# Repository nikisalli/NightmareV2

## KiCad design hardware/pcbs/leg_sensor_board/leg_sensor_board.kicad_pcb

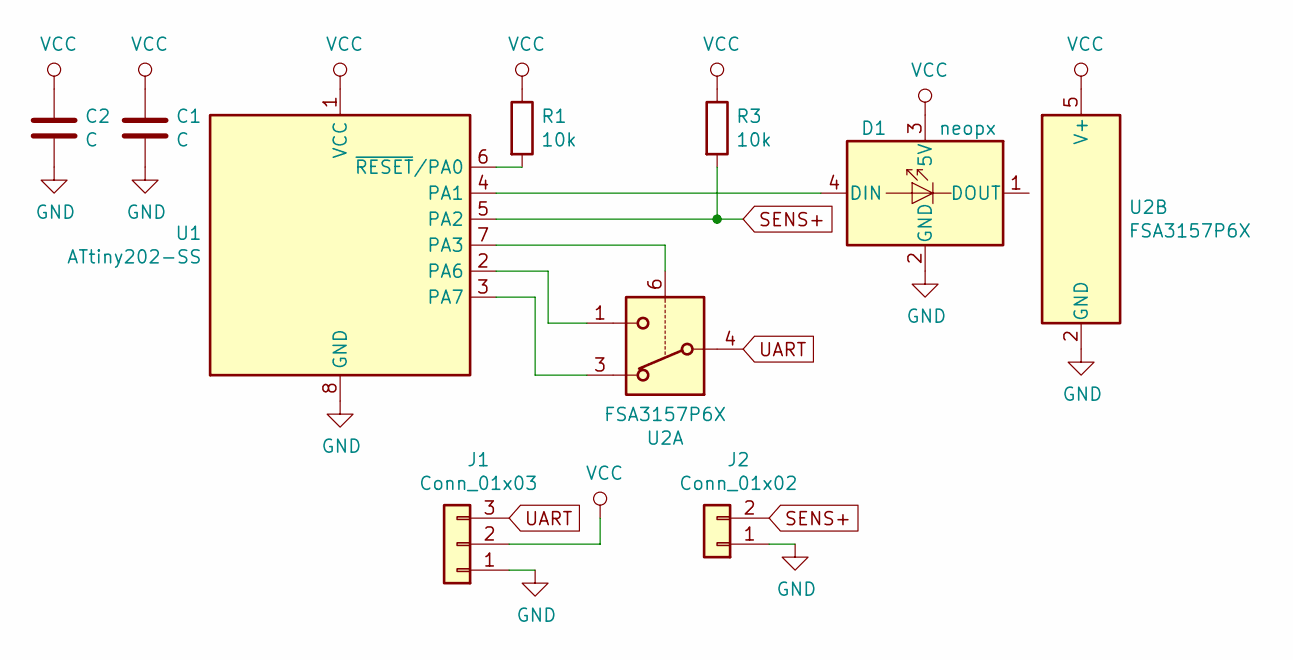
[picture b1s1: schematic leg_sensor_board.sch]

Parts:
C1, C2: C; C_0603_1608Metric
D1: neopx; LED_WS2812B_PLCC4_5.0x5.0mm_P3.2mm
J1: Conn_01x03; PinHeader_1x03_P2.54mm_Vertical
J2: Conn_01x02; PinHeader_1x02_P2.54mm_Vertical
R1, R3: 10k; R_0603_1608Metric
U1: ATtiny202-SS; SOIC-8_3.9x4.9mm_P1.27mm
U2: FSA3157P6X; SOT-363_SC-70-6

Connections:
GND: C1.2, C2.2, D1.2 (GND), J1.1, J2.1, U1.8 (GND), U2.2 (GND)
unnamed: D1.4 (DIN), U1.4 (PA1)
unnamed: R1.2, U1.6 (~RESET~/PA0)
unnamed: U1.2 (PA6), U2.1
unnamed: U1.3 (PA7), U2.3
unnamed: U1.7 (PA3), U2.6
SENS+: J2.2, R3.2, U1.5 (PA2)
UART: J1.3, U2.4
VCC: C1.1, C2.1, D1.3 (5V), J1.2, R1.1, R3.1, U1.1 (VCC), U2.5 (V+)

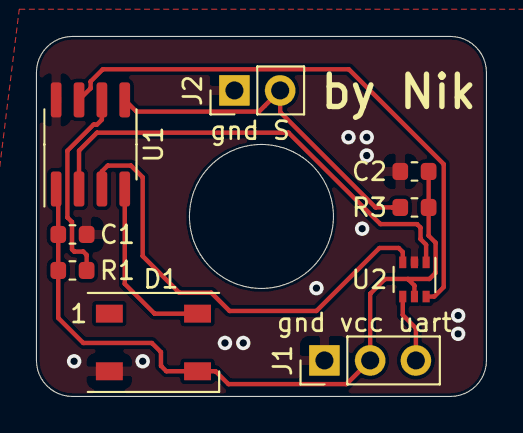
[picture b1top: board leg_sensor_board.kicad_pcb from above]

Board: 2 copper layers, 25.0 x 20.0 mm, 9 parts (0 on the bottom side), 9 nets.

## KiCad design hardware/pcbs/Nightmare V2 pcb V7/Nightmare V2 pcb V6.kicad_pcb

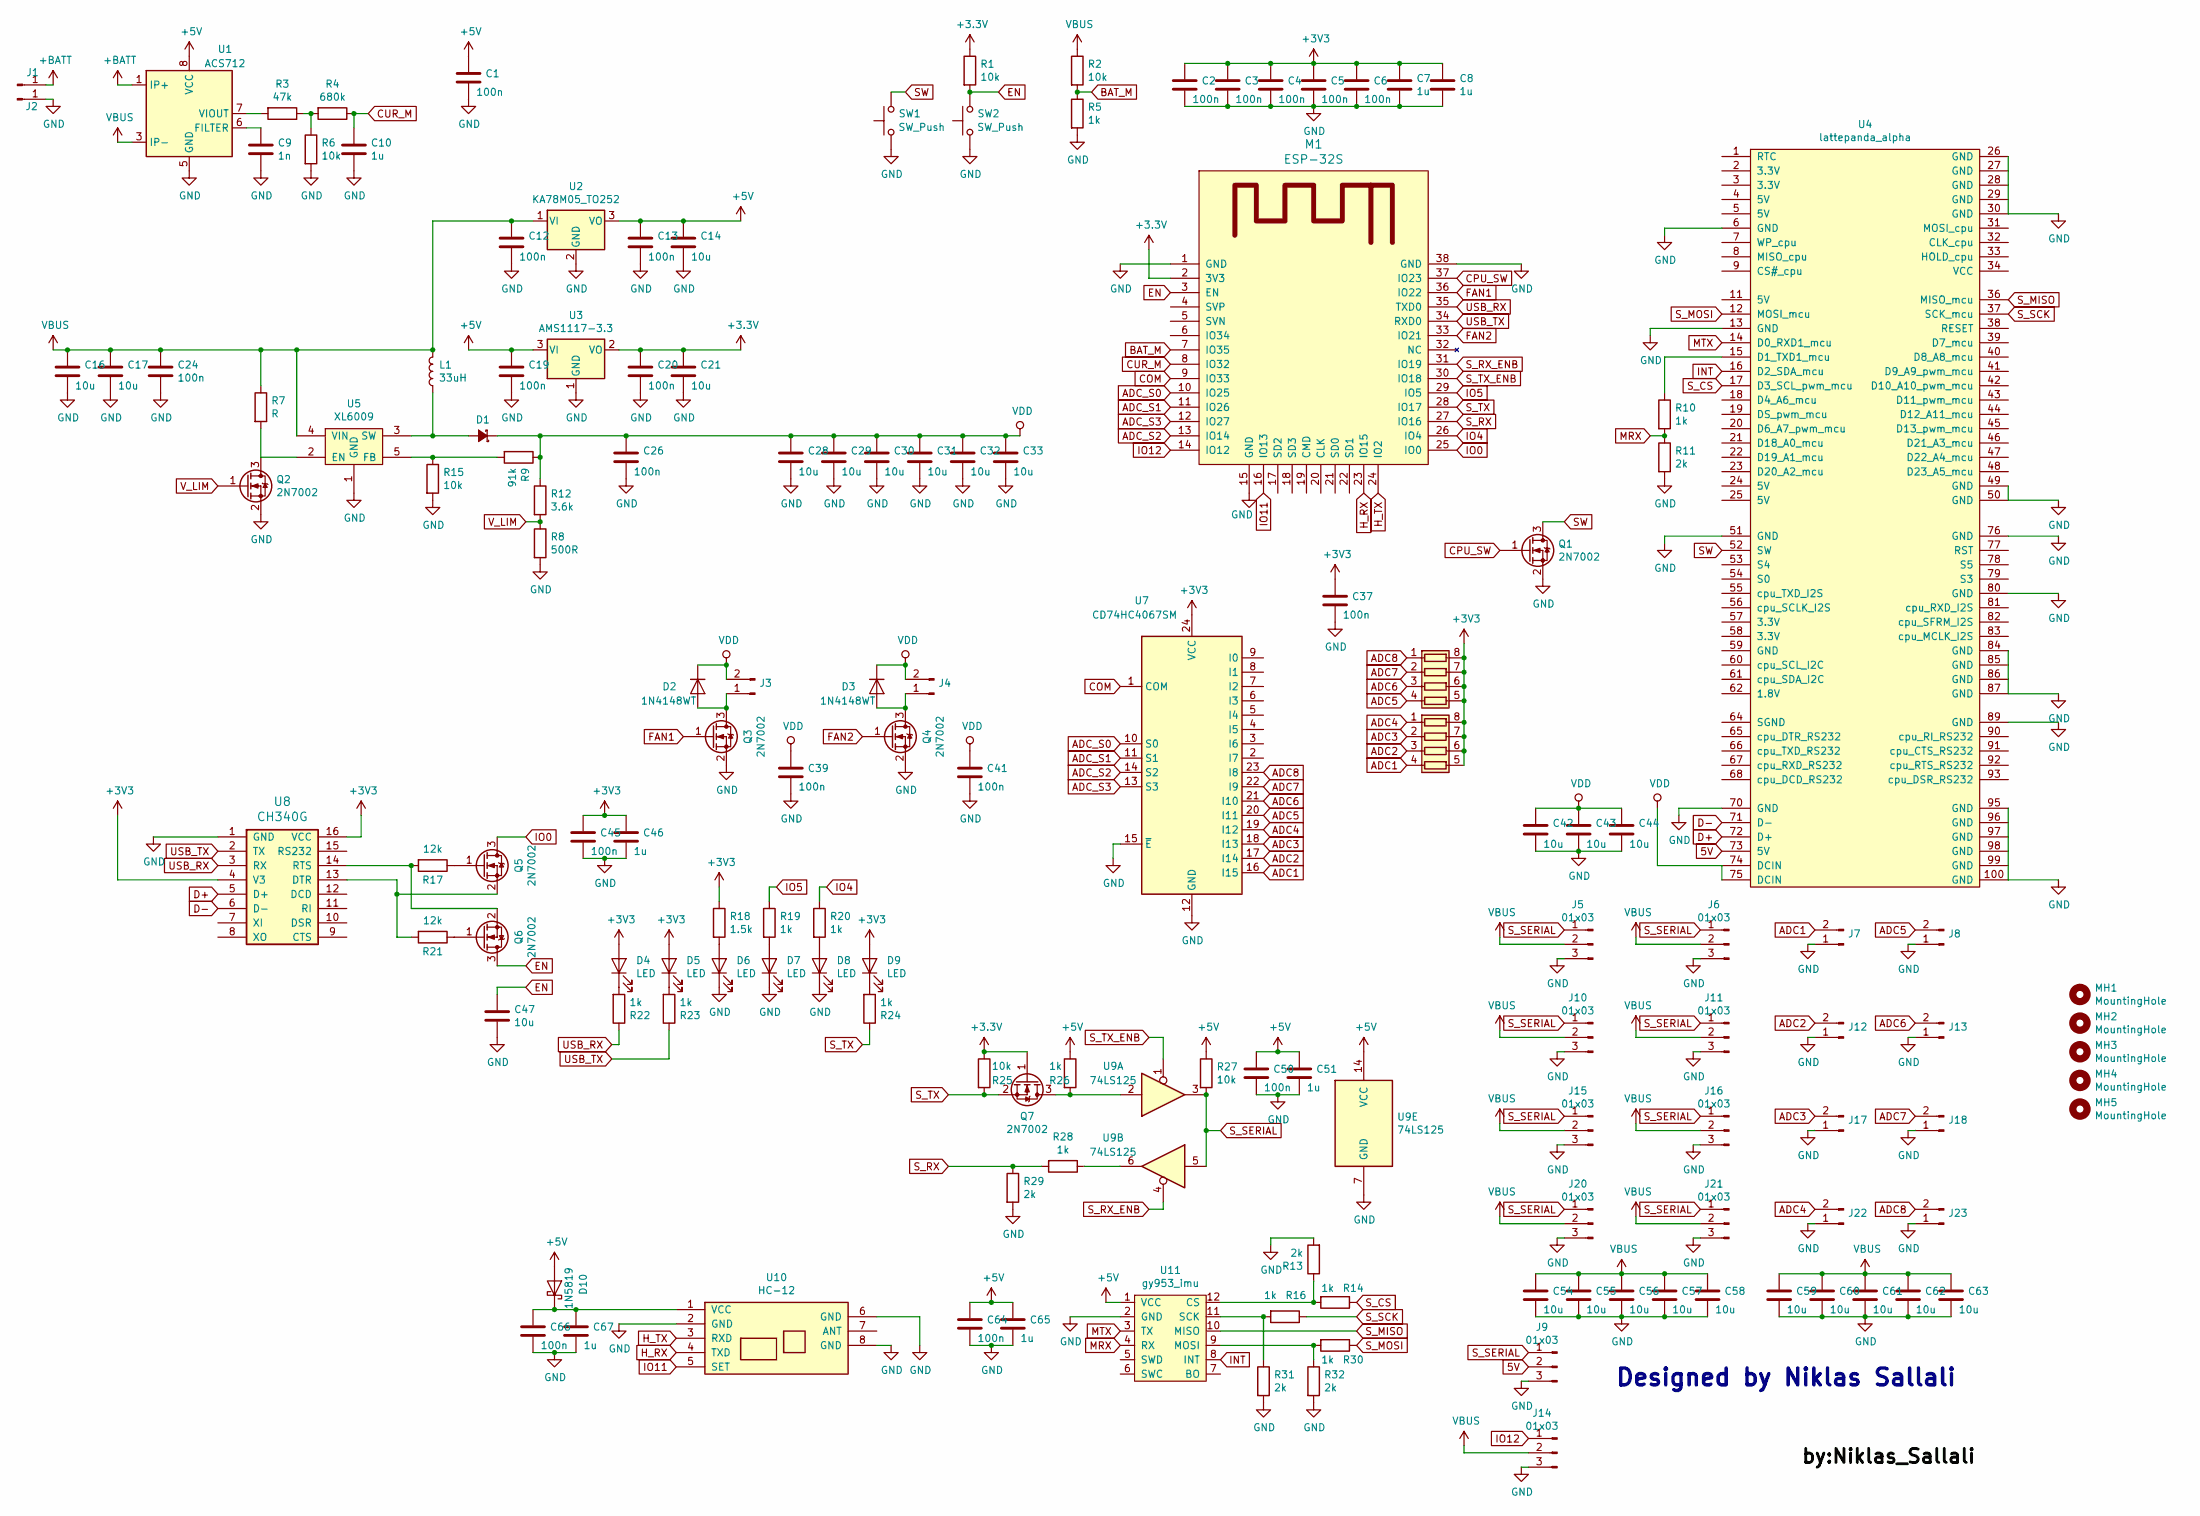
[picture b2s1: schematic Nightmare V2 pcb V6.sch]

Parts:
C1, C2, C3, C4, C5, C6, C12, C13, C19, C20, C24, C26, C37, C39, C41, C45, C50, C64, C66: 100n; C_0603_1608Metric
C7, C8, C10, C46, C51, C65, C67: 1u; C_0603_1608Metric
C9: 1n; C_0603_1608Metric
C14, C16, C17, C21, C28, C29, C30, C31, C32, C33, C42, C43, C44, C47, C54, C55, C56, C57, C58, C59, C60, C61, C62, C63: 10u; C_1206_3216Metric
D1: SS510; D_SMC; PartNumber LSM115JE3/TR13CT-ND
D2, D3: 1N4148WT; D_SOD-523
D4, D5, D6, D7, D8, D9: LED; LED_0603_1608Metric_Pad1.05x0.95mm_HandSolder
D10: 1N5819; D_SMA
J1, J2: Conn_01x01_Male; TestPoint_THTPad_4.0x4.0mm_Drill2.0mm
J3, J4: Conn_01x02_Male; JST_XH_B02B-XH-A_1x02_P2.50mm_Vertical
J5, J6, J9, J10, J11, J14, J15, J16, J20, J21: 01x03; JST_XH_B03B-XH-A_1x03_P2.50mm_Vertical
J7, J8, J12, J13, J17, J18, J22, J23: Conn_01x02_Male; JST_SH_BM02B-SRSS-TB_1x02-1MP_P1.00mm_Vertical
L1: 33uH; L_12x12mm_H6mm
M1: ESP-32S
MH1, MH2, MH3, MH4: MountingHole; MountingHole_3.2mm_M3_DIN965_Pad
MH5: MountingHole; nik_logo_15x13
Q1, Q2, Q3, Q4, Q5, Q6, Q7: 2N7002; SOT-23
R1, R2, R6, R15, R25, R27: 10k; R_0603_1608Metric
R3: 47k; R_0603_1608Metric
R4: 680k; R_0603_1608Metric
R5, R10, R14, R16, R19, R20, R22, R23, R24, R26, R28, R30: 1k; R_0603_1608Metric
R7: R; R_0603_1608Metric
R8: 500R; R_0603_1608Metric
R9: 91k; R_0603_1608Metric
R11, R13, R29, R31, R32: 2k; R_0603_1608Metric
R12: 3.6k; R_0603_1608Metric
R17, R21: 12k; R_0603_1608Metric
R18: 1.5k; R_0603_1608Metric
RN2, RN3: R_Pack04; R_Array_Convex_4x0603
SW1, SW2: SW_Push; SW_SPST_SKQG_WithoutStem
U1: ACS712; SOIC-8_3.9x4.9mm_P1.27mm
U2: KA78M05_TO252; TO-252-2
U3: AMS1117-3.3; SOT-223-3_TabPin2
U4: lattepanda_alpha
U5: XL6009; TO-263-5_TabPin3
U7: CD74HC4067SM; SSOP-24_5.3x8.2mm_P0.65mm
U8: CH340G; SOIC-16_3.9x9.9mm_P1.27mm
U9: 74LS125; SOIC-14_3.9x8.7mm_P1.27mm
U10: HC-12
U11: gy953_imu; GY953_IMU

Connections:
5V: J9.2, U4.73 (5V)
+5V: C1.1, C13.1, C14.1, C19.1, C50.1, C51.1, C64.1, C65.1, D10.2 (A), R26.1, R27.1, U1.8 (VCC), U2.3 (VO), U3.3 (VI), U9.14 (VCC), U11.1 (VCC)
+BATT: J1.1, U1.1 (IP+), U1.2 (IP+)
ADC1: J7.2, RN3.4 (R4.1), U7.16 (I15)
ADC2: J12.2, RN3.3 (R3.1), U7.17 (I14)
ADC3: J17.2, RN3.2 (R2.1), U7.18 (I13)
ADC4: J22.2, RN3.1 (R1.1), U7.19 (I12)
ADC5: J8.2, RN2.4 (R4.1), U7.20 (I11)
ADC6: J13.2, RN2.3 (R3.1), U7.21 (I10)
ADC7: J18.2, RN2.2 (R2.1), U7.22 (I9)
ADC8: J23.2, RN2.1 (R1.1), U7.23 (I8)
ADC_S0: M1.10 (IO25), U7.10 (S0)
ADC_S1: M1.11 (IO26), U7.11 (S1)
ADC_S2: M1.13 (IO14), U7.14 (S2)
ADC_S3: M1.12 (IO27), U7.13 (S3)
BAT_M: M1.7 (IO35), R2.2, R5.1
COM: M1.9 (IO33), U7.1 (COM)
CPU_SW: M1.37 (IO23), Q1.1 (G)
CUR_M: C10.1, M1.8 (IO32), R4.1
D+: U4.72 (D+), U8.5 (D+)
D-: U4.71 (D-), U8.6 (D-)
EN: C47.1, M1.3 (EN), Q6.3 (D), R1.2, SW2.2
FAN1: M1.36 (IO22), Q3.1 (G)
FAN2: M1.33 (IO21), Q4.1 (G)
GND: C1.2, C2.2, C3.2, C4.2, C5.2, C6.2, C7.2, C8.2, C9.2, C10.2, C12.2, C13.2, C14.2, C16.2, C17.2, C19.2, C20.2, C21.2, C24.2, C26.2, C28.2, C29.2, C30.2, C31.2, C32.2, C33.2, C37.2, C39.2, C41.2, C42.2, C43.2, C44.2, C45.2, C46.2, C47.2, C50.2, C51.2, C54.2, C55.2, C56.2, C57.2, C58.2, C59.2, C60.2, C61.2, C62.2, C63.2, C64.2, C65.2, C66.2, C67.2, D6.1 (K), D7.1 (K), D8.1 (K), J2.1, J5.3, J6.3, J7.1, J8.1, J9.3, J10.3, J11.3, J12.1, J13.1, J14.3, J15.3, J16.3, J17.1, J18.1, J20.3, J21.3, J22.1, J23.1, M1.1 (GND), M1.15 (GND), M1.38 (GND), Q1.2 (S), Q2.2 (S), Q3.2 (S), Q4.2 (S), R5.2, R6.2, R8.2, R11.2, R13.2, R15.2, R29.2, R31.2, R32.2, SW1.1, SW2.1, U1.5 (GND), U2.2 (GND), U3.1 (GND), U4.6 (GND), U4.13 (GND), U4.26 (GND), U4.30 (GND), U4.49 (GND), U4.50 (GND), U4.51 (GND), U4.70 (GND), U4.76 (GND), U4.80 (GND), U4.84 (GND), U4.87 (GND), U4.89 (GND), U4.95 (GND), U4.100 (GND), U5.1 (GND), U7.12 (GND), U7.15 (~E), U8.1 (GND), U9.7 (GND), U10.2 (GND), U10.6 (GND), U10.8 (GND), U11.2 (GND)
H_RX: M1.23 (IO15), U10.4 (TXD)
H_TX: M1.24 (IO2), U10.3 (RXD)
INT: U4.16 (D2_SDA_mcu), U11.8 (INT)
IO0: M1.25 (IO0), Q5.3 (D)
IO4: M1.26 (IO4), R20.1
IO5: M1.29 (IO5), R19.1
IO11: M1.16 (IO13), U10.5 (SET)
IO12: J14.1, M1.14 (IO12)
MRX: R10.2, R11.1, U11.4 (RX)
MTX: U4.14 (D0_RXD1_mcu), U11.3 (TX)
unnamed: C9.1, U1.6 (FILTER)
unnamed: C66.1, C67.1, D10.1 (K), U10.1 (VCC)
unnamed: D1.2 (A), L1.1, U5.3 (SW)
unnamed: D2.2 (A), J3.1, Q3.3 (D)
unnamed: D3.2 (A), J4.1, Q4.3 (D)
unnamed: D4.1 (K), R22.2
unnamed: D5.1 (K), R23.2
unnamed: D6.2 (A), R18.2
unnamed: D7.2 (A), R19.2
unnamed: D8.2 (A), R20.2
unnamed: D9.1 (K), R24.2
unnamed: Q2.3 (D), R7.2, U5.2 (EN)
unnamed: Q5.1 (G), R17.1
unnamed: Q5.2 (S), R21.2, U8.13 (DTR)
unnamed: Q6.1 (G), R21.1
unnamed: Q6.2 (S), R17.2, U8.14 (RTS)
unnamed: Q7.3 (D), R26.2, U9.2
unnamed: R3.1, R4.2, R6.1
unnamed: R3.2, U1.7 (VIOUT)
unnamed: R10.1, U4.15 (D1_TXD1_mcu)
unnamed: R13.1, R14.2, U11.12 (CS)
unnamed: R9.2, R15.1, U5.5 (FB)
unnamed: R16.2, R31.1, U11.11 (SCK)
unnamed: R28.1, U9.6
unnamed: R30.2, R32.1, U11.9 (MOSI)
SW: Q1.3 (D), SW1.2, U4.52 (SW)
S_CS: R14.1, U4.17 (D3_SCL_pwm_mcu)
S_MISO: U4.36 (MISO_mcu), U11.10 (MISO)
S_MOSI: R30.1, U4.12 (MOSI_mcu)
S_RX: M1.27 (IO16), R28.2, R29.1
S_RX_ENB: M1.31 (IO19), U9.4
S_SCK: R16.1, U4.37 (SCK_mcu)
S_SERIAL: J5.1, J6.1, J9.1, J10.1, J11.1, J15.1, J16.1, J20.1, J21.1, R27.2, U9.3, U9.5
S_TX: M1.28 (IO17), Q7.2 (S), R24.1, R25.2
S_TX_ENB: M1.30 (IO18), U9.1
USB_RX: M1.35 (TXD0), R22.1, U8.3 (RX)
USB_TX: M1.34 (RXD0), R23.1, U8.2 (TX)
VBUS: C12.1, C16.1, C17.1, C24.1, C54.1, C55.1, C56.1, C57.1, C58.1, C59.1, C60.1, C61.1, C62.1, C63.1, J5.2, J6.2, J10.2, J11.2, J14.2, J15.2, J16.2, J20.2, J21.2, L1.2, R2.1, R7.1, U1.3 (IP-), U1.4 (IP-), U2.1 (VI), U5.4 (VIN)
VDD: C26.1, C28.1, C29.1, C30.1, C31.1, C32.1, C33.1, C39.1, C41.1, C42.1, C43.1, C44.1, D1.1 (K), D2.1 (K), D3.1 (K), J3.2, J4.2, R9.1, R12.1, U4.74 (DCIN), U4.75 (DCIN)
V_LIM: Q2.1 (G), R8.1, R12.2

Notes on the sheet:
Designed by Niklas Sallali

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
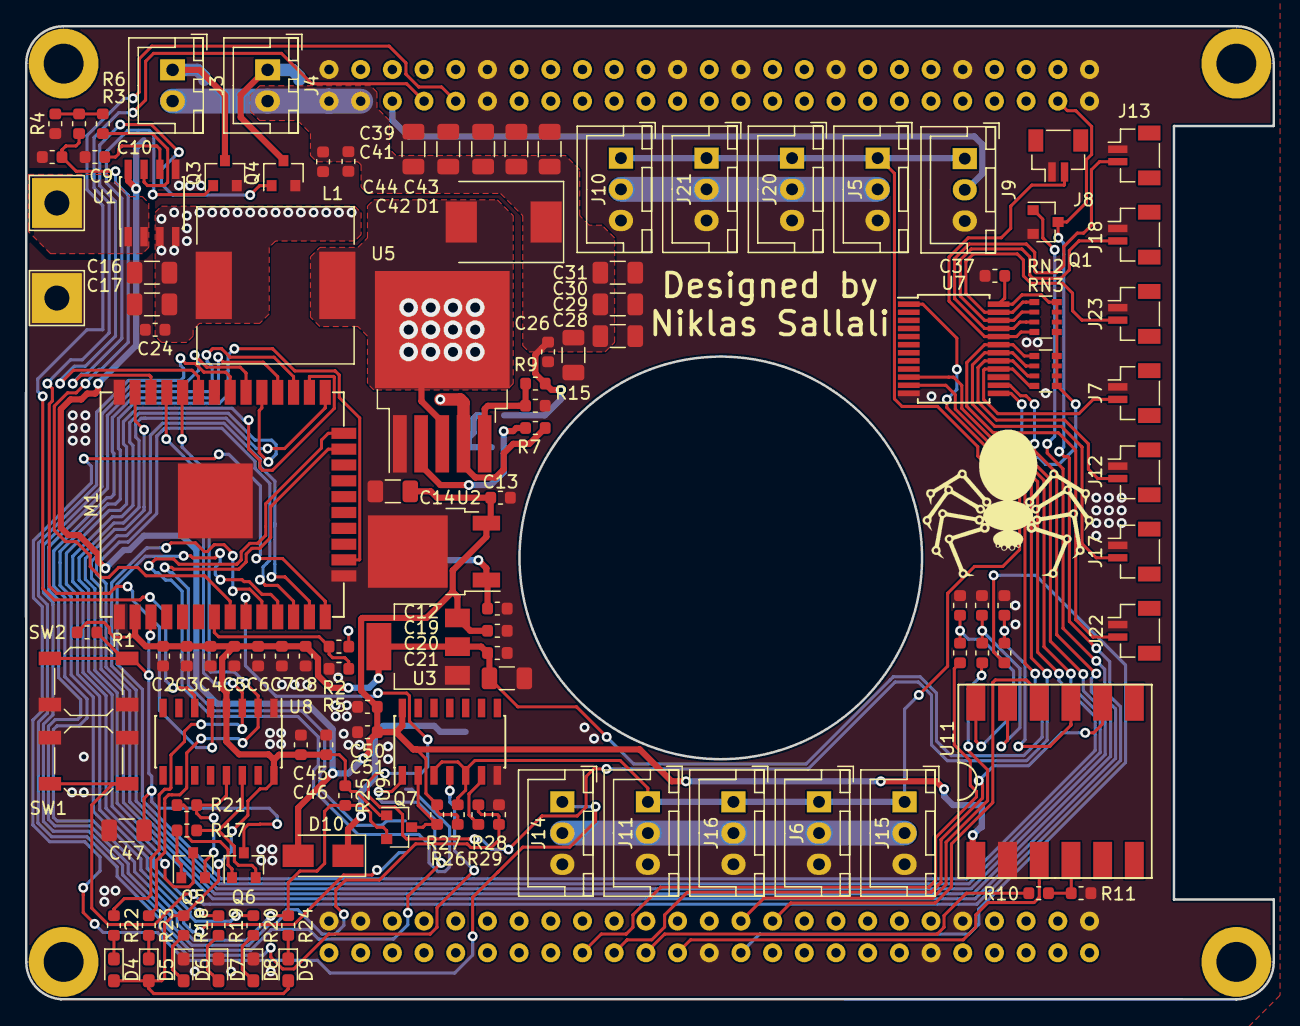
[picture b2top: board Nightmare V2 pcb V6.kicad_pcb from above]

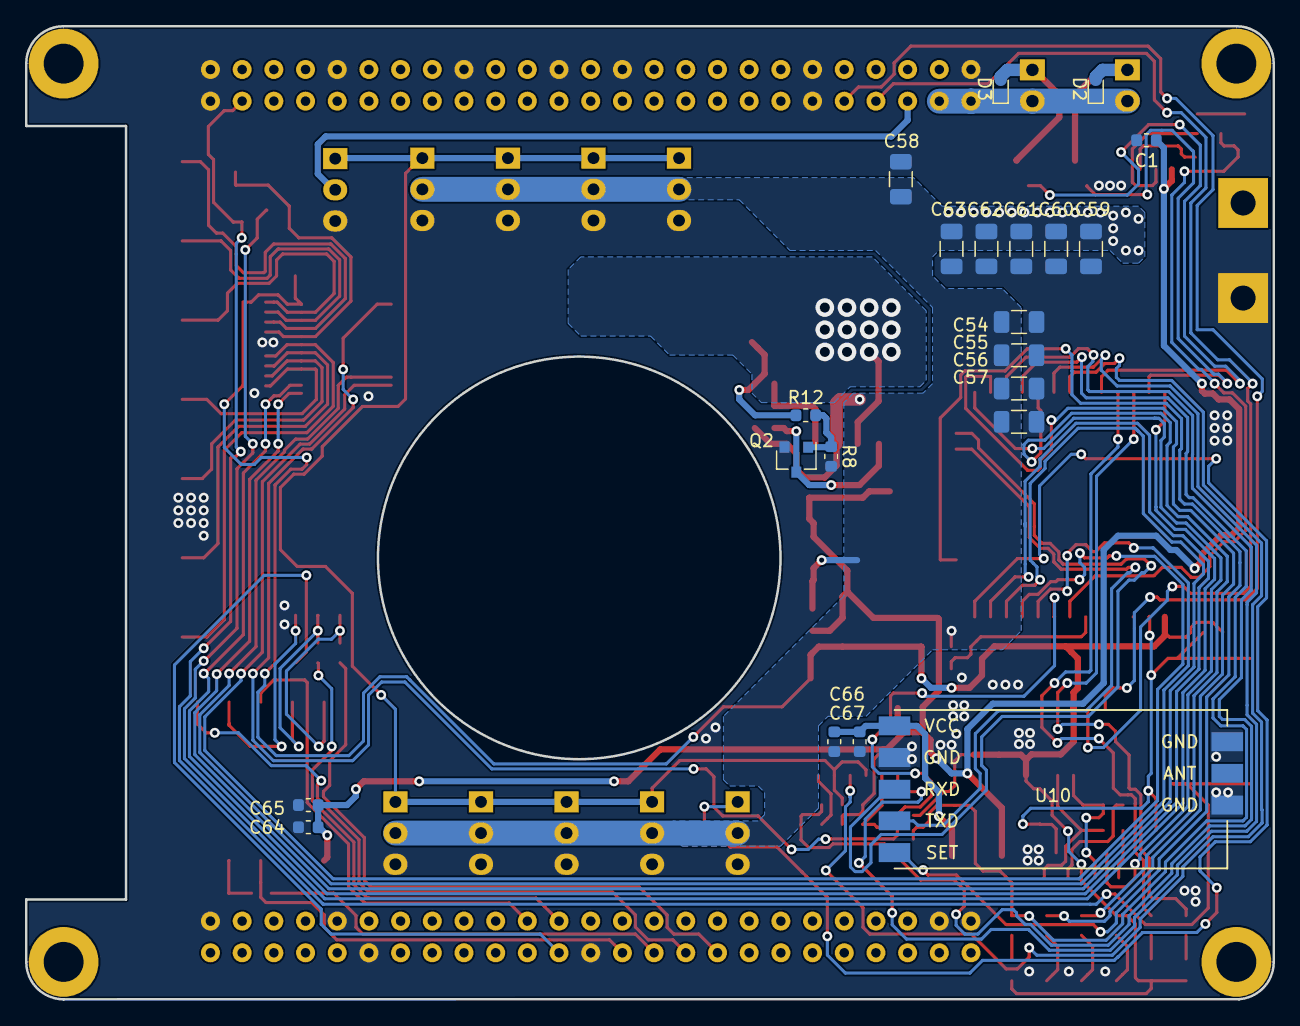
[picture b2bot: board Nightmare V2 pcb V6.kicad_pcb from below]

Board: 2 copper layers, 100.0 x 78.0 mm, 143 parts (21 on the bottom side), 76 nets.

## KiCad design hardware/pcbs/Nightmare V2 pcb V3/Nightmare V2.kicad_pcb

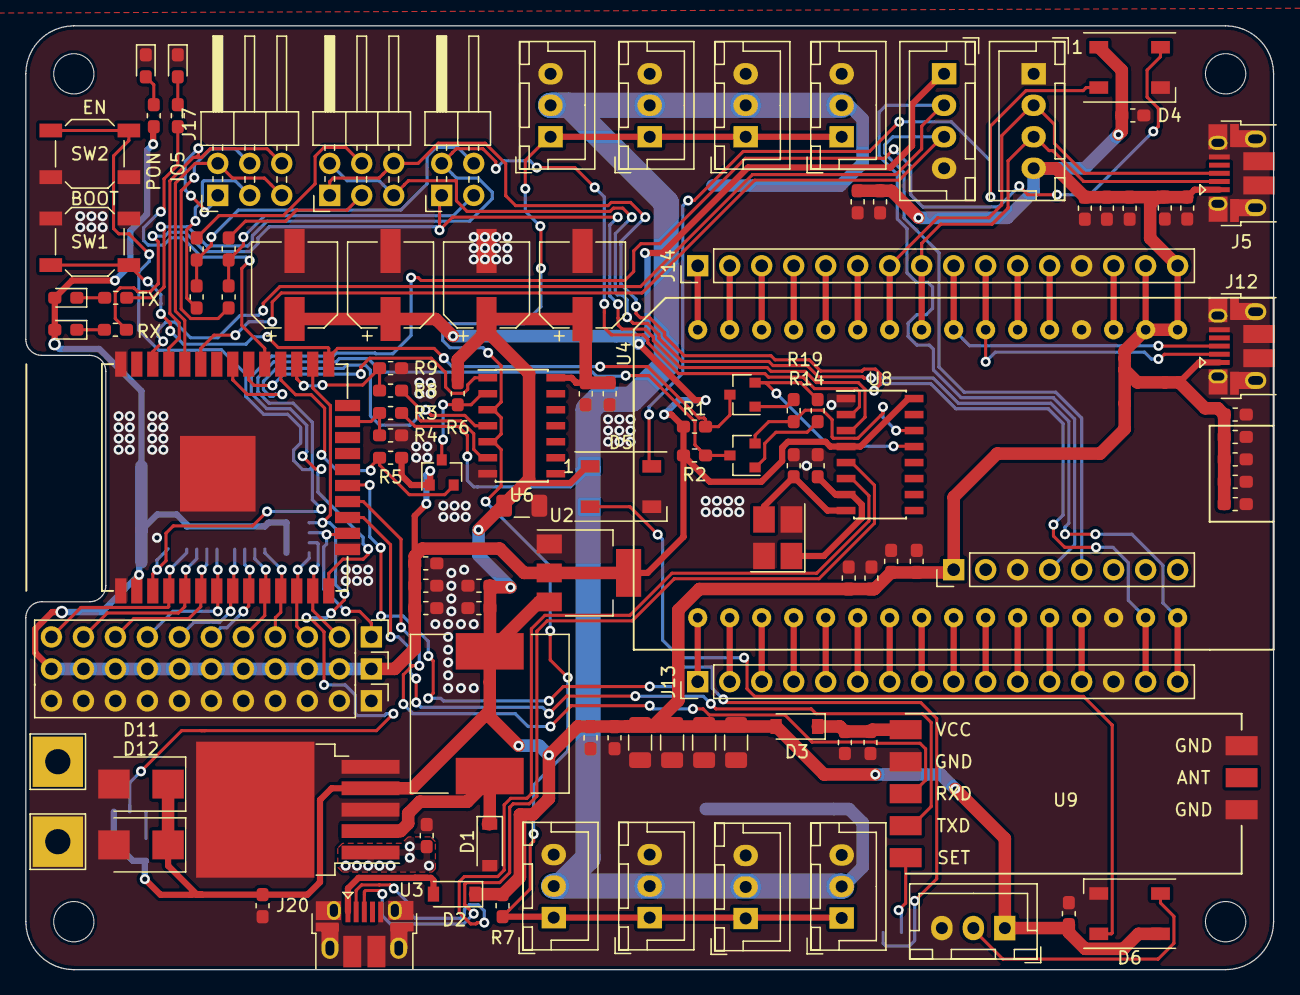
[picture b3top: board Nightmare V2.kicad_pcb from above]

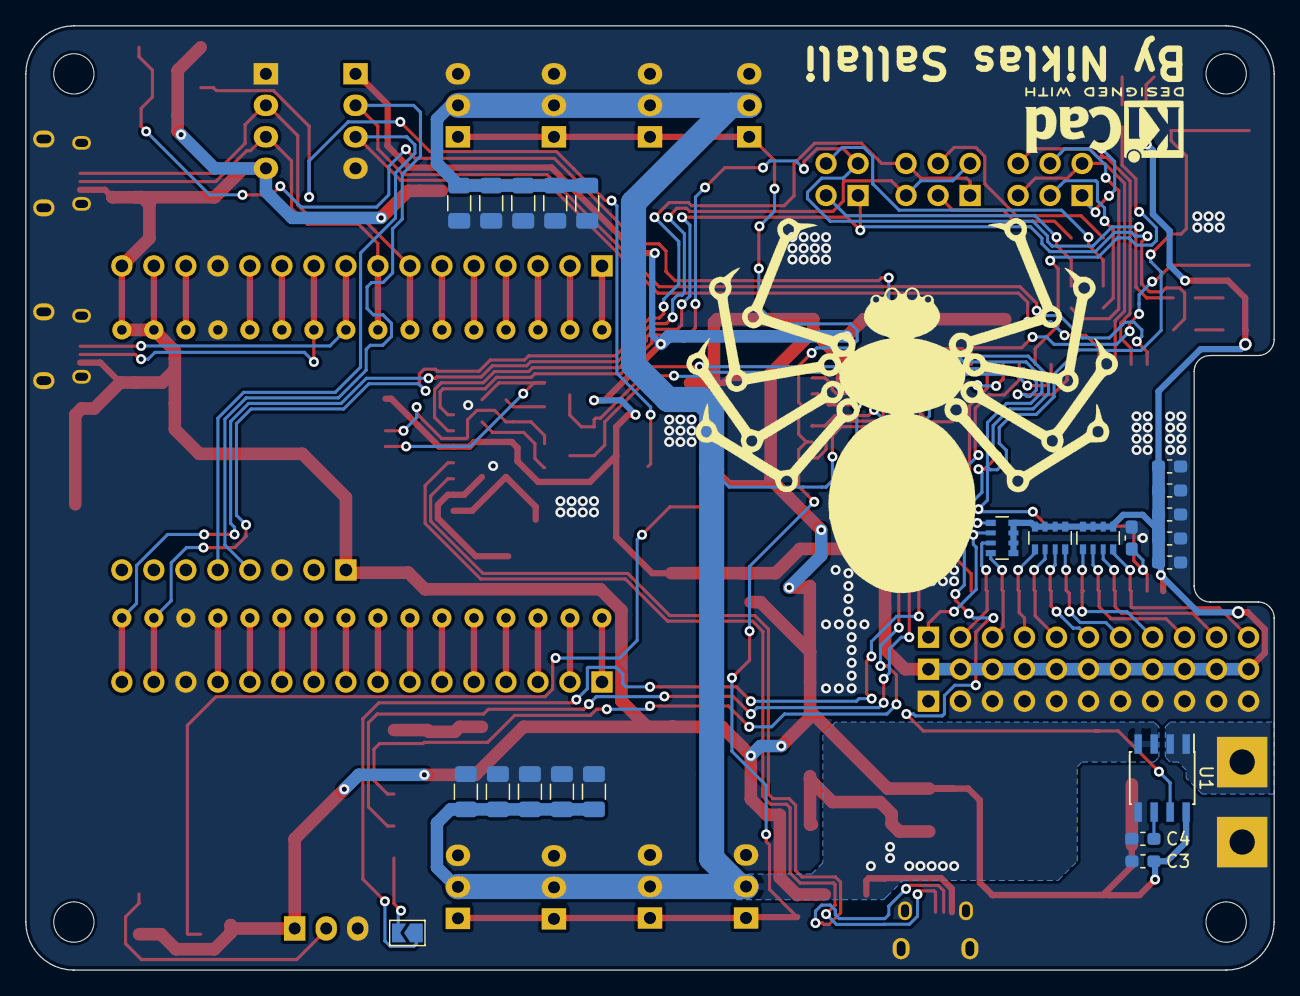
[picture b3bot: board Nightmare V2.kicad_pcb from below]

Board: 2 copper layers, 99.1 x 74.9 mm, 139 parts (25 on the bottom side), 92 nets.

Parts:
C1, C10, C11, C12, C18, C40, C46, C48, C49, C53, C55, C57, C59: 1u; C_0603_1608Metric_Pad1.05x0.95mm_HandSolder
C2, C3, C5, C6, C7, C8, C9, C14, C15, C17, C20, C31, C33, C34, C35, C36, C37, C38, C39, C45, C47, C52, C54, C56, C58: 100n; C_0603_1608Metric_Pad1.05x0.95mm_HandSolder
C4: 1n; C_0603_1608Metric_Pad1.05x0.95mm_HandSolder
C13, C16, C19, C32: 220u; CP_Elec_6.3x7.7
C21, C22, C23, C24, C25, C26, C27, C28, C29, C30, C41, C42, C43, C44, C60: 10u; C_1206_3216Metric
C50, C51: 22p; C_0603_1608Metric_Pad1.05x0.95mm_HandSolder
D1, D2, D3: 1N5819; D_SOD-123
D4, D5, D6: WS2812B; LED_WS2812B_PLCC4_5.0x5.0mm_P3.2mm
D7, D8, D9, D10: LED; LED_0603_1608Metric_Pad1.05x0.95mm_HandSolder
D11, D12: 5.1V; D_SMB
J1, J2, J6, J7, J8, J9, J10, J11: 01x03; JST_XH_B03B-XH-A_1x03_P2.50mm_Vertical
J3, J18: Conn_01x04_Male; JST_XH_B04B-XH-A_1x04_P2.50mm_Vertical
J5, J12, J20: USB_B_Micro; USB_Micro-B_Amphenol_10103594-0001LF_Horizontal
J13, J14: Conn_01x16_Female; PinHeader_1x16_P2.54mm_Vertical
J16: Conn_01x08_Male; PinHeader_1x08_P2.54mm_Vertical
J17, J19: J; PinHeader_2x03_P2.54mm_Horizontal
J21: Conn_01x03_Male; JST_XH_B03B-XH-A_1x03_P2.50mm_Vertical
J22: Conn_02x02_Counter_Clockwise; PinHeader_2x02_P2.54mm_Horizontal
J24, J25: Conn_01x01_Male; TestPoint_THTPad_4.0x4.0mm_Drill2.0mm
JP1: Jumper_NO_Small; SolderJumper-2_P1.3mm_Open_TrianglePad1.0x1.5mm
L1: 33uH; L_12x12mm_H8mm
M1: ESP-32S
MH1, MH2, MH3, MH4: MountingHole; MountingHole_3.2mm_M3_DIN965
MH5: MountingHole; nik_logo_38x32
MH6: MountingHole; KiCad-Logo2_6mm_SilkScreen
Q2: 2N7002; SOT-23
Q4, Q5: S8050; SOT-23
R1, R2, R3, R5, R7: 10k; R_0603_1608Metric_Pad1.05x0.95mm_HandSolder
R4, R6, R8, R10, R11, R12, R13, R15, R16, R18: 1k; R_0603_1608Metric_Pad1.05x0.95mm_HandSolder
R9: 2k; R_0603_1608Metric_Pad1.05x0.95mm_HandSolder
R14, R19: 12k; R_0603_1608Metric_Pad1.05x0.95mm_HandSolder
R17: 1.5k; R_0603_1608Metric_Pad1.05x0.95mm_HandSolder
RN1, RN2, RN3: R_Pack04; R_Array_Convex_4x0603
SW1, SW2: SW_Push; SW_SPST_SKQG_WithStem
U1: ACS712; SOIC-8_3.9x4.9mm_P1.27mm
U2: AMS1117-3.3; SOT-223-3_TabPin2
U3: LM2596S-5; TO-263-5_TabPin3
U4: NanoPi_duo
U6: 74LS125; SOIC-14_3.9x8.7mm_P1.27mm
U8: CH340G; SOIC-16_3.9x9.9mm_P1.27mm
U9: HC-12
U10: 03x11_vertical_connector; PinHeader_3x11_P2.54mm_Vertical
Y1: 12Mhz; Crystal_SMD_SeikoEpson_TSX3225-4Pin_3.2x2.5mm_HandSoldering

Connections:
+3V3: C1.1, C2.1, C5.1, C6.1, C7.1, C10.1, C11.1, C15.1, C16.1, C19.1, D7.2, D8.2, J18.1, M1.2, Q2.1, R1.1, R2.1, R5.1, R17.1, RN1.5, RN1.6, RN1.7, RN1.8, RN2.5, RN2.6, RN2.7, RN2.8, RN3.5, RN3.6, RN3.7, RN3.8, U2.2, U8.4, U8.16, U10.12, U10.13, U10.14, U10.15, U10.16, U10.17, U10.18, U10.19, U10.20, U10.21, U10.22
+5V: C3.1, C8.1, C9.1, C12.1, C13.1, C14.1, C17.1, C18.1, C31.1, C32.1, C33.1, C34.1, C35.1, C36.1, C37.1, C38.1, C39.1, C40.1, C41.1, C42.1, C43.1, C44.1, C45.1, C46.1, C52.1, C53.1, C54.1, C55.1, C56.1, C57.1, C58.1, C59.1, C60.1, D2.1, D3.2, D4.1, D5.1, D6.1, D11.1, D12.1, J3.4, J5.1, J12.1, J14.15, J14.16, J16.1, J21.1, L1.2, R6.1, R7.1, U1.8, U2.3, U3.4, U4.17, U4.18, U6.14
+BATT: J24.1, U1.1, U1.2
ADC1: M1.4, RN1.4, U10.11
ADC2: M1.5, RN1.3, U10.10
ADC3: M1.6, RN1.2, U10.9
ADC4: M1.7, RN1.1, U10.8
ADC5: M1.8, RN2.4, U10.7
ADC6: M1.9, RN2.3, U10.6
ADC7: M1.10, RN2.2, U10.5
ADC8: M1.11, RN2.1, U10.4
ADC9: M1.12, RN3.4, U10.3
ADC10: M1.13, RN3.3, U10.2
ADC11: M1.16, RN3.2, U10.1
ADC13: M1.23, R3.2, R4.1
ADC15: M1.26, RN3.1, U1.7
EN: C49.1, M1.3, Q5.3, R2.2, SW2.2
ESP_RX: J17.2, J17.5, M1.34
ESP_TX: J17.1, J17.6, M1.35
GND: C1.2, C2.2, C3.2, C4.2, C5.2, C6.2, C7.2, C8.2, C9.2, C10.2, C11.2, C12.2, C13.2, C14.2, C15.2, C16.2, C17.2, C18.2, C19.2, C20.2, C21.2, C22.2, C23.2, C24.2, C25.2, C26.2, C27.2, C28.2, C29.2, C30.2, C31.2, C32.2, C33.2, C34.2, C35.2, C36.2, C37.2, C38.2, C39.2, C40.2, C41.2, C42.2, C43.2, C44.2, C45.2, C46.2, C47.2, C48.2, C49.2, C50.2, C51.2, C52.2, C53.2, C54.2, C55.2, C56.2, C57.2, C58.2, C59.2, C60.2, D1.2, D4.3, D5.3, D6.3, D9.1, D10.1, D11.2, D12.2, J1.3, J2.3, J3.1, J5.5, J5.6, J6.3, J7.3, J8.3, J9.3, J10.3, J11.3, J12.5, J12.6, J13.14, J14.13, J16.3, J18.4, J20.5, J20.6, J21.3, J25.1, M1.1, M1.15, M1.38, R4.2, R9.2, SW1.1, SW2.1, U1.5, U2.1, U3.3, U3.5, U4.14, U4.20, U6.7, U8.1, U9.2, U9.6, U9.8, U10.23, U10.24, U10.25, U10.26, U10.27, U10.28, U10.29, U10.30, U10.31, U10.32, U10.33, Y1.2, Y1.4
H_RX: M1.17, U9.4
H_TX: M1.18, U9.3
IO0: M1.25, Q4.3, R1.2, SW1.2
IO5: M1.29, R18.1
IO11: JP1.1, M1.19
LED_IO: D4.4, M1.14
LED_O: D6.2, J21.2
NP_RX: J13.16, J19.2, J19.5, U4.16
NP_TX: J13.15, J19.1, J19.6, U4.15
unnamed: C4.1, U1.6
unnamed: C47.1, C48.1, D3.1, U9.1
unnamed: C50.1, U8.7, Y1.1
unnamed: C51.1, U8.8, Y1.3
unnamed: D1.1, L1.1, U3.2
unnamed: D2.2, J20.1
unnamed: D4.2, D5.4
unnamed: D5.2, D6.4
unnamed: D7.1, R15.2
unnamed: D8.1, R16.2
unnamed: D9.2, R17.2
unnamed: D10.2, R18.2
unnamed: J13.1, U4.1
unnamed: J13.2, U4.2
unnamed: J13.3, U4.3
unnamed: J13.4, U4.4
unnamed: J13.5, U4.5
unnamed: J13.6, U4.6
unnamed: J13.7, U4.7
unnamed: J13.8, U4.8
unnamed: J13.9, U4.9
unnamed: J13.10, U4.10
unnamed: J13.11, U4.11
unnamed: J13.12, U4.12
unnamed: J13.13, U4.13
unnamed: J14.1, U4.32
unnamed: J14.2, U4.31
unnamed: J14.3, U4.30
unnamed: J14.4, U4.29
unnamed: J14.5, U4.28
unnamed: J14.6, U4.27
unnamed: J14.11, U4.22
unnamed: J14.12, U4.21
unnamed: J14.14, U4.19
unnamed: J17.3, R10.1
unnamed: J17.4, R11.1
unnamed: J19.3, R13.2
unnamed: J19.4, R12.2
unnamed: J20.2, U8.6
unnamed: J20.3, U8.5
unnamed: J22.3, R11.2, R13.1
unnamed: J22.4, R10.2, R12.1
unnamed: JP1.2, U9.5
unnamed: Q2.3, R6.2, U6.2
unnamed: Q4.1, R14.1
unnamed: Q4.2, R19.2, U8.13
unnamed: Q5.1, R19.1
unnamed: Q5.2, R14.2, U8.14
unnamed: R8.1, U6.6
SCL: J16.4, J18.2, M1.36
SDA: J16.5, J18.3, M1.33
S_RX: M1.27, R8.2, R9.1
S_RX_ENB: M1.31, U6.4
S_SERIAL: J1.1, J2.1, J6.1, J7.1, J8.1, J9.1, J10.1, J11.1, R7.2, U6.3, U6.5
S_TX: M1.28, Q2.2, R5.2
S_TX_ENB: M1.30, U6.1
USB1+: J12.3, J14.9, U4.24
USB1-: J12.2, J14.10, U4.23
USB2+: J3.2, J5.3, J14.7, U4.26
USB2-: J3.3, J5.2, J14.8, U4.25
USB_RX: J22.1, R15.1, U8.3
USB_TX: J22.2, R16.1, U8.2
VBUS: C20.1, C21.1, C22.1, C23.1, C24.1, C25.1, C26.1, C27.1, C28.1, C29.1, C30.1, J1.2, J2.2, J6.2, J7.2, J8.2, J9.2, J10.2, J11.2, R3.1, U1.3, U1.4, U3.1

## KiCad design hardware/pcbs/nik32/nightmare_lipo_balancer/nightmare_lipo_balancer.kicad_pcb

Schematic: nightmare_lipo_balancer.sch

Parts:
BT1, BT2: Battery_Cell; SolderWirePad_1x02_P3.81mm_Drill1.2mm
C1, C2, C3, C5, C7, C8, C13, C14, C15, C16: 10u; C_1206_3216Metric_Pad1.42x1.75mm_HandSolder
C4, C6, C9, C17, C26: 1u; C_0603_1608Metric_Pad1.05x0.95mm_HandSolder
C10, C11, C21, C25, C27, C28: 0.1u; C_0603_1608Metric_Pad1.05x0.95mm_HandSolder
C12: 6.8n; C_0603_1608Metric_Pad1.05x0.95mm_HandSolder
C18, C23: 220u; CP_Elec_6.3x7.7
C19: 33p; C_0603_1608Metric_Pad1.05x0.95mm_HandSolder
C20: 10n; C_0603_1608Metric_Pad1.05x0.95mm_HandSolder
C22: 100p; C_0603_1608Metric_Pad1.05x0.95mm_HandSolder
D1: 1n5819; D_SMA
D2, D3: TL431DBV; SOT-23-5
D4: 1N4148WT; D_SOD-523
D5: TL431; SOT-23-5
D6, D7: LED; LED_0603_1608Metric_Pad1.05x0.95mm_HandSolder
L1: 3.3uH; L_12x12mm_H8mm
MH1, MH2, MH3, MH4: MountingHole; MountingHole_3.5mm_Pad_Via
MH5, MH6: MountingHole; TestPoint_THTPad_4.0x4.0mm_Drill2.0mm
MH7: MountingHole; nik_logo_19x16
Q1: PSMN1R5; LFPAK56
Q2: PSMN8R3; LFPAK56
Q3, Q5: DMP3099L; SOT-23
Q6, Q7: 2N3906; SOT-23
Q8: 2N7002; SOT-23
R1: 15R; R_1206_3216Metric
R2, R5, R31: 10k; R_0603_1608Metric
R3, R12, R17: 220k; R_0603_1608Metric
R4, R7, R11, R13: 1k; R_0603_1608Metric
R6: 1.8k; R_0603_1608Metric
R8, R18: 330k; R_0603_1608Metric
R9, R10, R19, R20: 15R; R_2816_7142Metric
R14, R23, R27, R29: 2.2k; R_0603_1608Metric
R15: 100R; R_0603_1608Metric
R16, R21, R22: 1M; R_0603_1608Metric
R24: 0.01R; R_2816_7142Metric
R25: 10R; R_0603_1608Metric
R26, R28, R30: 100k; R_0603_1608Metric
RV1: TRIM; Potentiometer_Bourns_3296P_Horizontal
RV4: 10k; Potentiometer_Bourns_3296P_Horizontal
U1: L78L05_SOT89; SOT-89-3
U2: NCP3020; SOIC-8_3.9x4.9mm_P1.27mm
U3: LM358; SOIC-8_3.9x4.9mm_P1.27mm
U4: P_MOS_LFPAK56; LFPAK56

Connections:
5V: C6.1, C7.1, C8.1, C26.1, C27.1, R14.1, R23.1, U1.1 (OUT), U3.8 (V+)
+BATT: BT1.1, Q3.2, Q7.1, R3.1, R4.1, U4.1, U4.2, U4.3
FB: C21.1, D4.1, R7.2, R11.1, R31.2, U2.3
GND: C1.2, C2.2, C3.2, C4.2, C5.2, C6.2, C7.2, C8.2, C9.2, C10.2, C13.2, C14.2, C15.2, C16.2, C17.2, C18.2, C19.2, C20.2, C21.2, C23.2, C25.2, C26.2, C27.2, C28.2, D5.5, MH6.1, Q2.1, Q2.2, Q2.3, Q8.2 (S), R6.2, R11.2, R21.2, R22.2, R24.2, R26.2, R29.1, RV4.3, U1.2 (GND), U2.4, U3.4 (V-)
I_FB: BT2.2, D3.5, R18.2, R19.2, R20.2, R24.1, R25.2
unnamed: BT1.2, BT2.1, D2.5, Q5.2, R8.2, R9.2, R10.2, R12.1, R13.1
unnamed: C11.1, U2.8
unnamed: C11.2, L1.1, Q1.1, Q1.2, Q1.3, Q2.5, R2.2, U2.6
unnamed: C12.2, R7.1
unnamed: C19.1, R5.1, U2.2
unnamed: C20.1, R5.2
unnamed: C22.1, R15.2, R27.1, U3.1
unnamed: C22.2, R27.2, R28.1, U3.2 (-)
unnamed: C25.1, D5.3, D5.4, R14.2, R17.1
unnamed: C28.1, R16.2, R26.1, U3.6 (-)
unnamed: D1.1, R1.2, U2.7
unnamed: D1.2, Q1.4, R1.1, R2.1
unnamed: D2.3, Q3.1, R4.2
unnamed: D2.4, R3.2, R8.1
unnamed: D3.3, Q5.1, R13.2
unnamed: D3.4, R12.2, R18.1
unnamed: D4.2, R15.1
unnamed: D6.1, Q8.1 (G), U3.7
unnamed: D6.2, D7.2, R23.2
unnamed: D7.1, Q8.3 (D)
unnamed: Q2.4, R6.1, U2.5
unnamed: Q3.3, R9.1, R10.1
unnamed: Q5.3, R19.1, R20.1
unnamed: Q6.2, Q6.3, Q7.2, R21.1
unnamed: Q7.3, R22.1, U4.4
unnamed: R16.1, R28.2, RV4.2
unnamed: R17.2, RV4.1
unnamed: R25.1, R30.1, U3.5 (+)
unnamed: R29.2, R30.2, U3.3 (+)
unnamed: R31.1, RV1.2, RV1.3
VCC: C12.1, C13.1, C14.1, C15.1, C16.1, C17.1, C18.1, C23.1, L1.2, Q6.1, RV1.1, U4.5
VIN: C1.1, C2.1, C3.1, C4.1, C5.1, C9.1, C10.1, MH5.1, Q1.5, U1.3 (IN), U2.1

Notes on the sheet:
Designed by Niklas Sallali
I SET
V SET

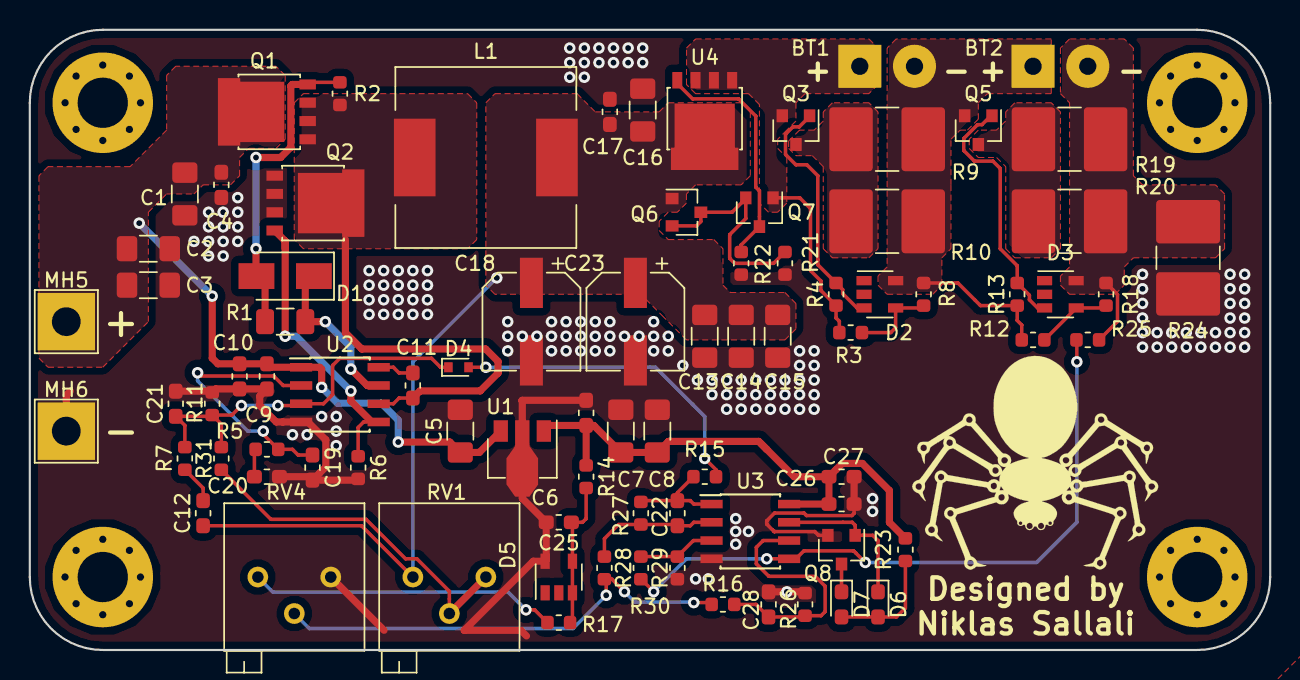
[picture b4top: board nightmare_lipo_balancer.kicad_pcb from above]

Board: 2 copper layers, 86.4 x 43.2 mm, 88 parts (0 on the bottom side), 37 nets.
